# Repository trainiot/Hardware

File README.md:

# Hardware
This git repository contains hardware I am designing to run my small internet connected model train layout.

* [SPI 2 DCC](Spi2Dcc)  
Generates the DCC signal. Controlled through SPI.

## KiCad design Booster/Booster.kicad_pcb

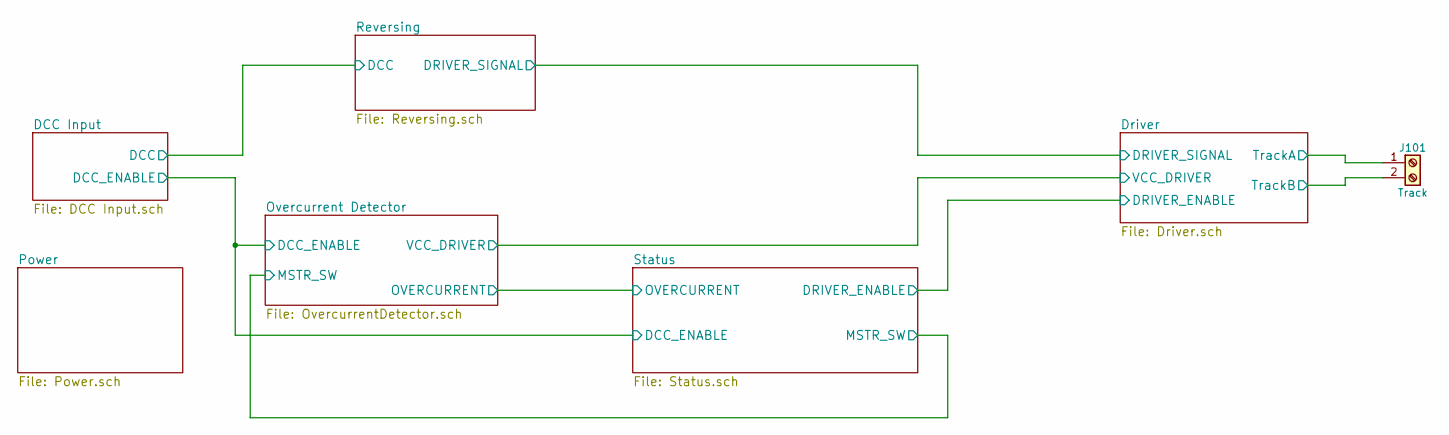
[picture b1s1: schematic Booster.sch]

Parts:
J101: Track; TerminalBlock_bornier-2_P5.08mm

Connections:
/Driver/TrackA: J101.1; also elsewhere on the board
/Driver/TrackB: J101.2; also elsewhere on the board

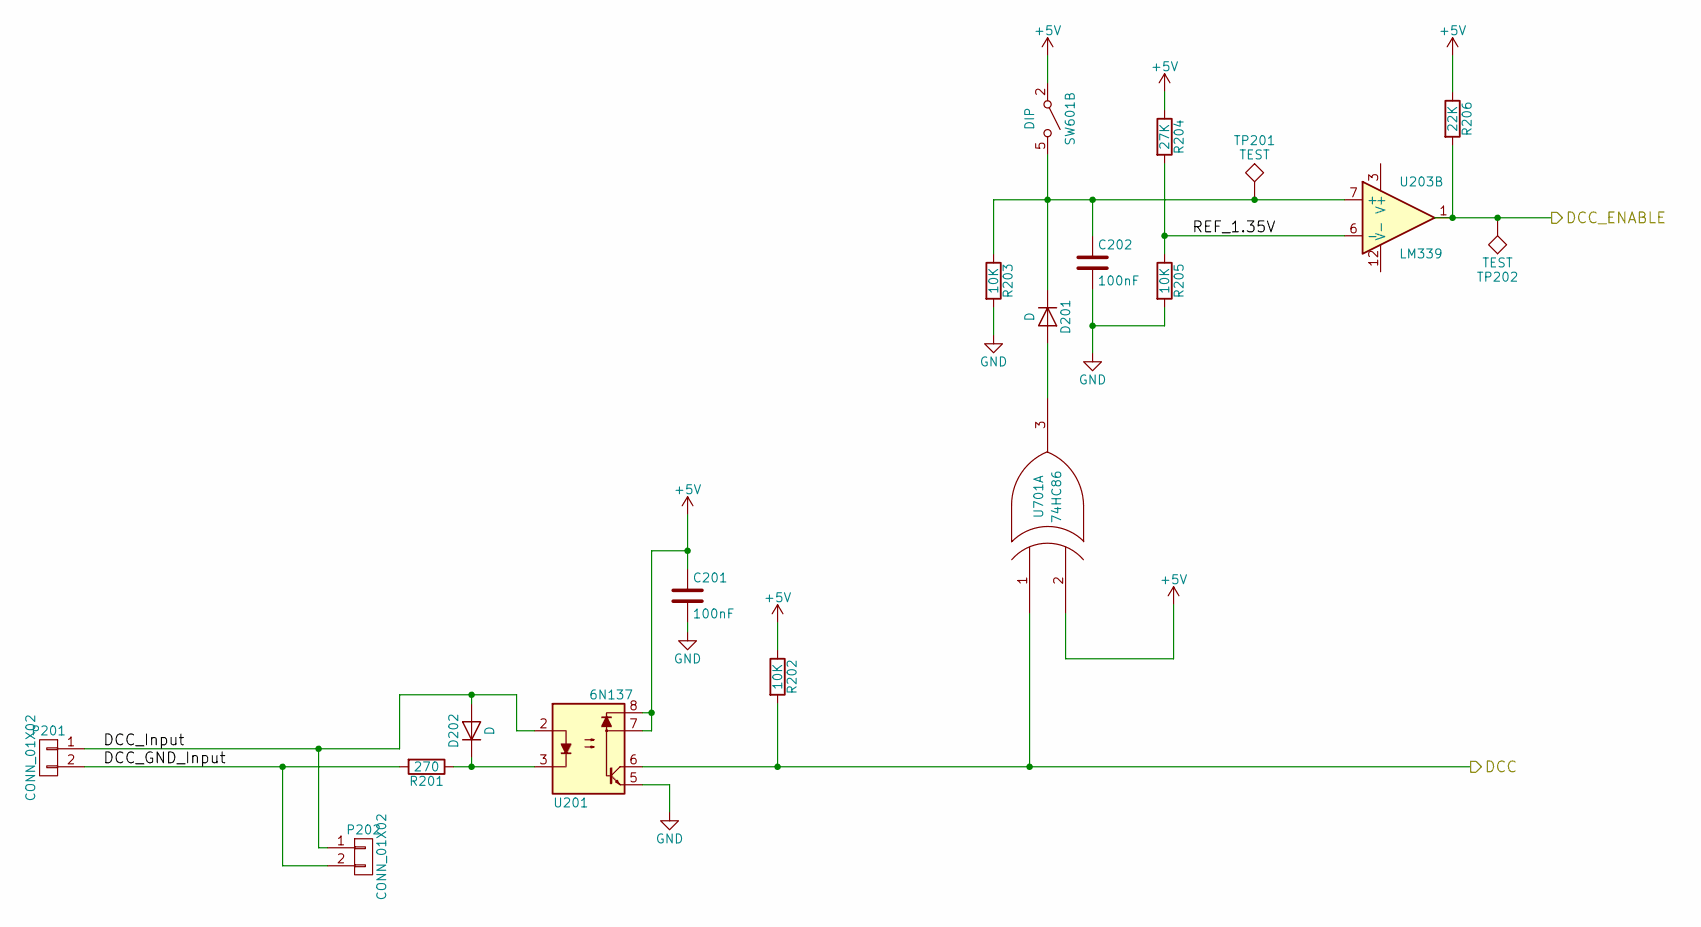
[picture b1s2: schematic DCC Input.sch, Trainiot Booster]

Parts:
C201: 100nF; TO-220-2_Vertical
C202: 100nF; C_0805
D201, D202: D; D_MiniMELF
P201, P202: CONN_01X02; JST_XH_B02B-XH-A_02x2.50mm_Straight
R201: 270; R_0805
R202, R203, R205: 10K; R_0805
R204: 27K; R_0805
R206: 22K; R_0805
SW601: DIP; SW_DIP_x3_W7.62mm_Slide
TP201, TP202: TEST; Measurement_Point_Round-TH_Small
U201: 6N137; SMDIP-8_W9.53mm_Clearance8mm
U203: LM339; SOIC-14_N
U701: 74HC86; SOIC-14_N

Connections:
+5V: C201.1, R202.1, R204.1, R206.1, SW601.2 (A), U201.7, U201.8, U701.2 (IN2), U701.14 (VCC); also elsewhere on the board
+15V: U203.3 (V+); also elsewhere on the board
/DCC Input/DCC: R202.2, U201.6, U701.1 (IN1); also elsewhere on the board
/DCC Input/DCC_ENABLE: R206.2, TP202.1, U203.1; also elsewhere on the board
/DCC Input/DCC_GND_Input: P201.2, P202.2, R201.2
/DCC Input/DCC_Input: D202.2 (A), P201.1, P202.1, U201.2
/DCC Input/REF_1.35V: R204.2, R205.1, U203.6 (-)
GND: C201.2, C202.2, R203.2, R205.2, U201.5, U203.12 (V-), U701.7 (GND); also elsewhere on the board
unnamed: C202.1, D201.1 (K), R203.1, SW601.5 (B), TP201.1, U203.7 (+)
unnamed: D201.2 (A), U701.3 (OUT)
unnamed: D202.1 (K), R201.1, U201.3

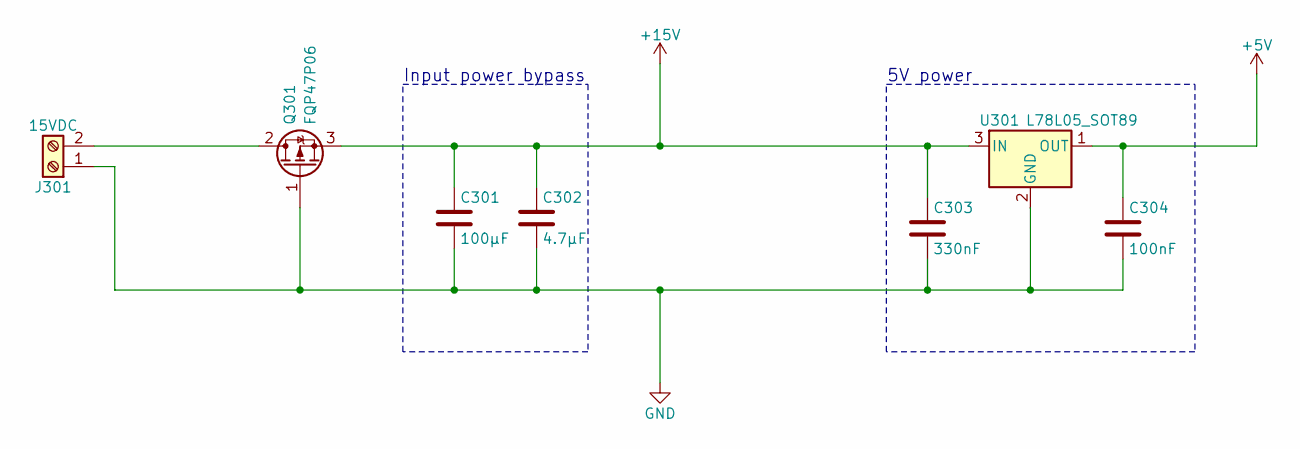
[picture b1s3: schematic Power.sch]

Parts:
C301: 100µF; CP_Radial_D6.3mm_P2.50mm
C302: 4.7µF; CP_Radial_D5.0mm_P2.00mm
C303: 330nF; C_0805
C304: 100nF; C_0805
J301: 15VDC; TerminalBlock_bornier-2_P5.08mm
Q301: FQP47P06; TO-220-3_Vertical
U301: L78L05_SOT89; SOT-89-3

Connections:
+5V: C304.1, U301.1 (OUT); also elsewhere on the board
+15V: C301.1, C302.1, C303.1, Q301.3 (S), U301.3 (IN); also elsewhere on the board
GND: C301.2, C302.2, C303.2, C304.2, J301.1, Q301.1 (G), U301.2 (GND); also elsewhere on the board
unnamed: J301.2, Q301.2 (D)

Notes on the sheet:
Input power bypass
5V power

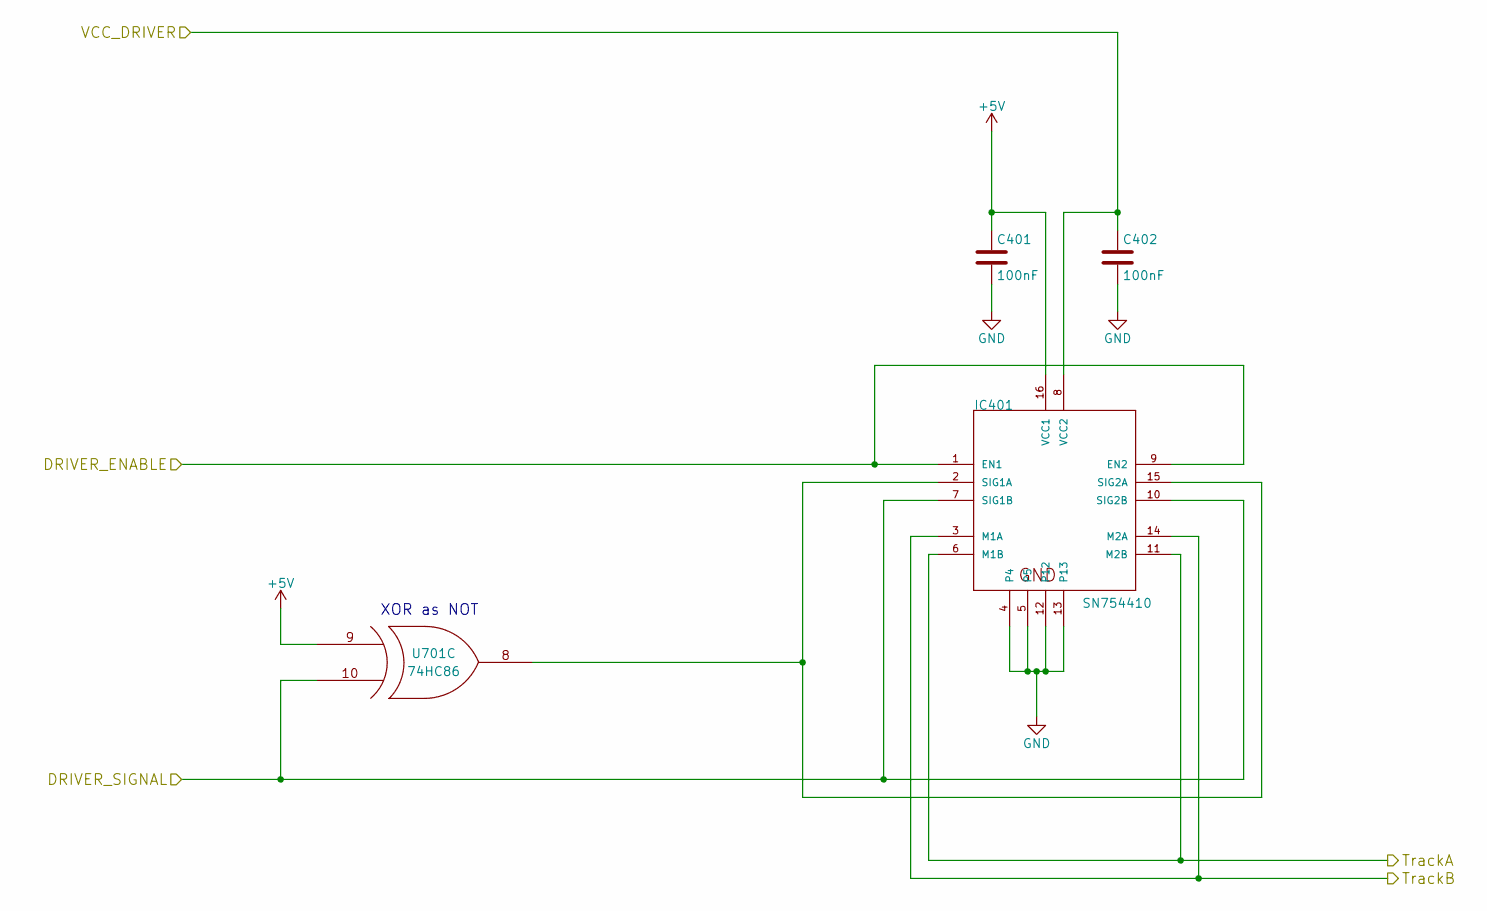
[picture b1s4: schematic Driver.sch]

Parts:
C401, C402: 100nF; C_0805
IC401: SN754410; DIP-16_W7.62mm
U701: 74HC86; SOIC-14_N

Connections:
+5V: C401.1, IC401.16 (VCC1), U701.9 (IN1), U701.14 (VCC); also elsewhere on the board
/Driver/DRIVER_ENABLE: IC401.1 (EN1), IC401.9 (EN2); also elsewhere on the board
/Driver/DRIVER_SIGNAL: IC401.7 (SIG1B), IC401.10 (SIG2B), U701.10 (IN2); also elsewhere on the board
/Driver/TrackA: IC401.6 (M1B), IC401.11 (M2B); also elsewhere on the board
/Driver/TrackB: IC401.3 (M1A), IC401.14 (M2A); also elsewhere on the board
/Driver/VCC_DRIVER: C402.1, IC401.8 (VCC2); also elsewhere on the board
GND: C401.2, C402.2, IC401.4, IC401.5, IC401.12, IC401.13, U701.7 (GND); also elsewhere on the board
unnamed: IC401.2 (SIG1A), IC401.15 (SIG2A), U701.8 (OUT)

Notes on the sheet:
XOR as NOT

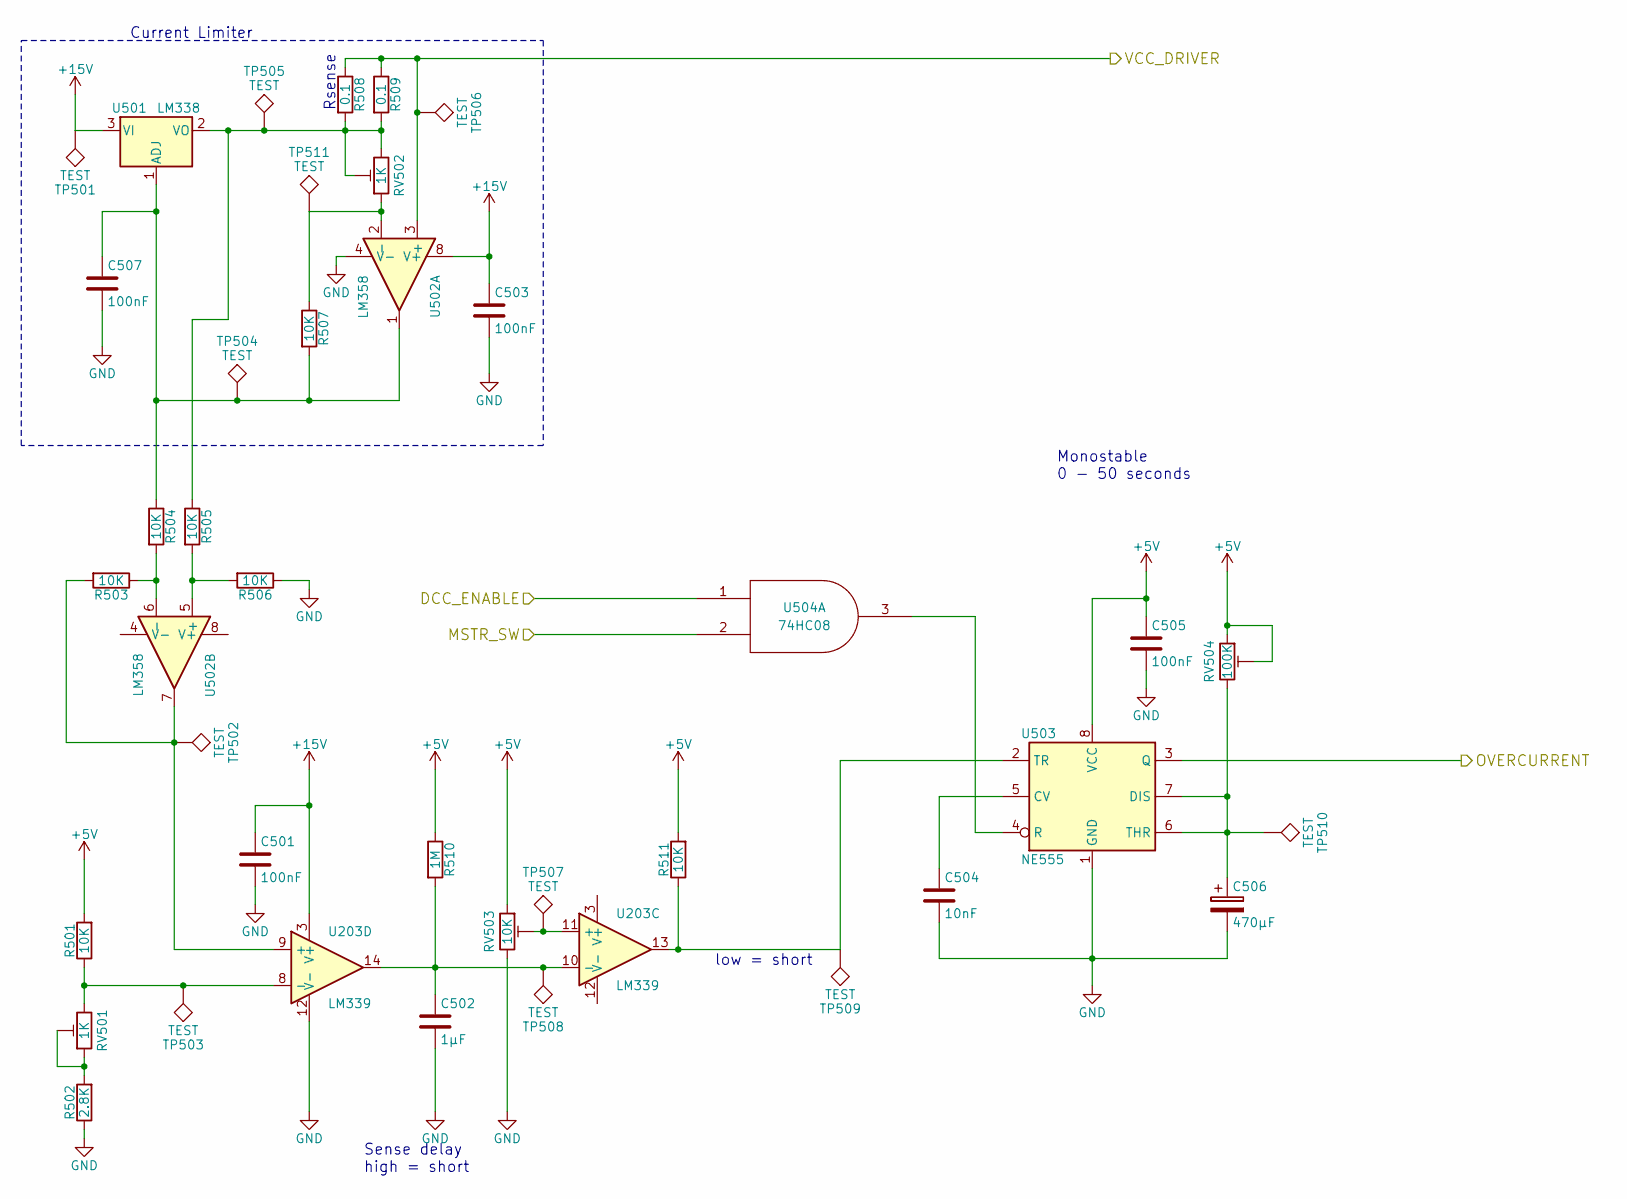
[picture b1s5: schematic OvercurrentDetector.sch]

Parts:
C501, C503, C505, C507: 100nF; C_0805
C502: 1µF; CP_Radial_D5.0mm_P2.50mm
C504: 10nF; C_0805
C506: 470µF; CP_Radial_D10.0mm_P5.00mm
R501, R503, R504, R505, R506, R507, R511: 10K; R_0805
R502: 2.8K; R_0805
R508, R509: 0.1; R_Axial_DIN0207_L6.3mm_D2.5mm_P7.62mm_Horizontal
R510: 1M; R_0805
RV501, RV502: 1K; Potentiometer_Trimmer_Bourns_3296W
RV503: 10K; Potentiometer_Trimmer_Bourns_3296W
RV504: 100K; Potentiometer_Trimmer_Bourns_3296W
TP501, TP502, TP503, TP504, TP505, TP506, TP507, TP508, TP509, TP510, TP511: TEST; Measurement_Point_Round-TH_Small
U203: LM339; SOIC-14_N
U501: LM338; TO-220-3_Vertical_Single_Pin_Heatshield
U502: LM358; SOIC-8-N
U503: NE555; SOIC-8-N
U504: 74HC08; SOIC-14_N

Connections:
+5V: C505.1, R501.2, R510.1, R511.2, RV503.1, RV504.1, RV504.2, U503.8 (VCC), U504.14 (VCC); also elsewhere on the board
+15V: C501.1, C503.1, TP501.1, U203.3 (V+), U501.3 (VI), U502.8 (V+); also elsewhere on the board
/DCC Input/DCC_ENABLE: U504.1; also elsewhere on the board
/Driver/VCC_DRIVER: R508.1, R509.1, TP506.1, U502.3 (+); also elsewhere on the board
/Overcurrent Detector/MSTR_SW: U504.2; also elsewhere on the board
/Overcurrent Detector/OVERCURRENT: U503.3 (Q); also elsewhere on the board
GND: C501.2, C502.2, C503.2, C504.2, C505.2, C506.2, C507.2, R502.1, R506.1, RV503.3, U203.12 (V-), U502.4 (V-), U503.1 (GND), U504.7 (GND); also elsewhere on the board
unnamed: C502.1, R510.2, TP508.1, U203.10 (-), U203.14
unnamed: C504.1, U503.5 (CV)
unnamed: C506.1, RV504.3, TP510.1, U503.6 (THR), U503.7 (DIS)
unnamed: C507.1, R504.1, R507.2, TP504.1, U501.1 (ADJ), U502.1
unnamed: R501.1, RV501.3, TP503.1, U203.8 (-)
unnamed: R502.2, RV501.1, RV501.2
unnamed: R503.1, R504.2, U502.6 (-)
unnamed: R503.2, TP502.1, U203.9 (+), U502.7
unnamed: R505.1, R508.2, R509.2, RV502.2, RV502.3, TP505.1, U501.2 (VO)
unnamed: R505.2, R506.2, U502.5 (+)
unnamed: R507.1, RV502.1, TP511.1, U502.2 (-)
unnamed: R511.1, TP509.1, U203.13, U503.2 (TR)
unnamed: RV503.2, TP507.1, U203.11 (+)
unnamed: U503.4 (R), U504.3

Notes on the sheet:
Current Limiter
Rsense
Sense delay high = short
low = short
Monostable 0 - 50 seconds

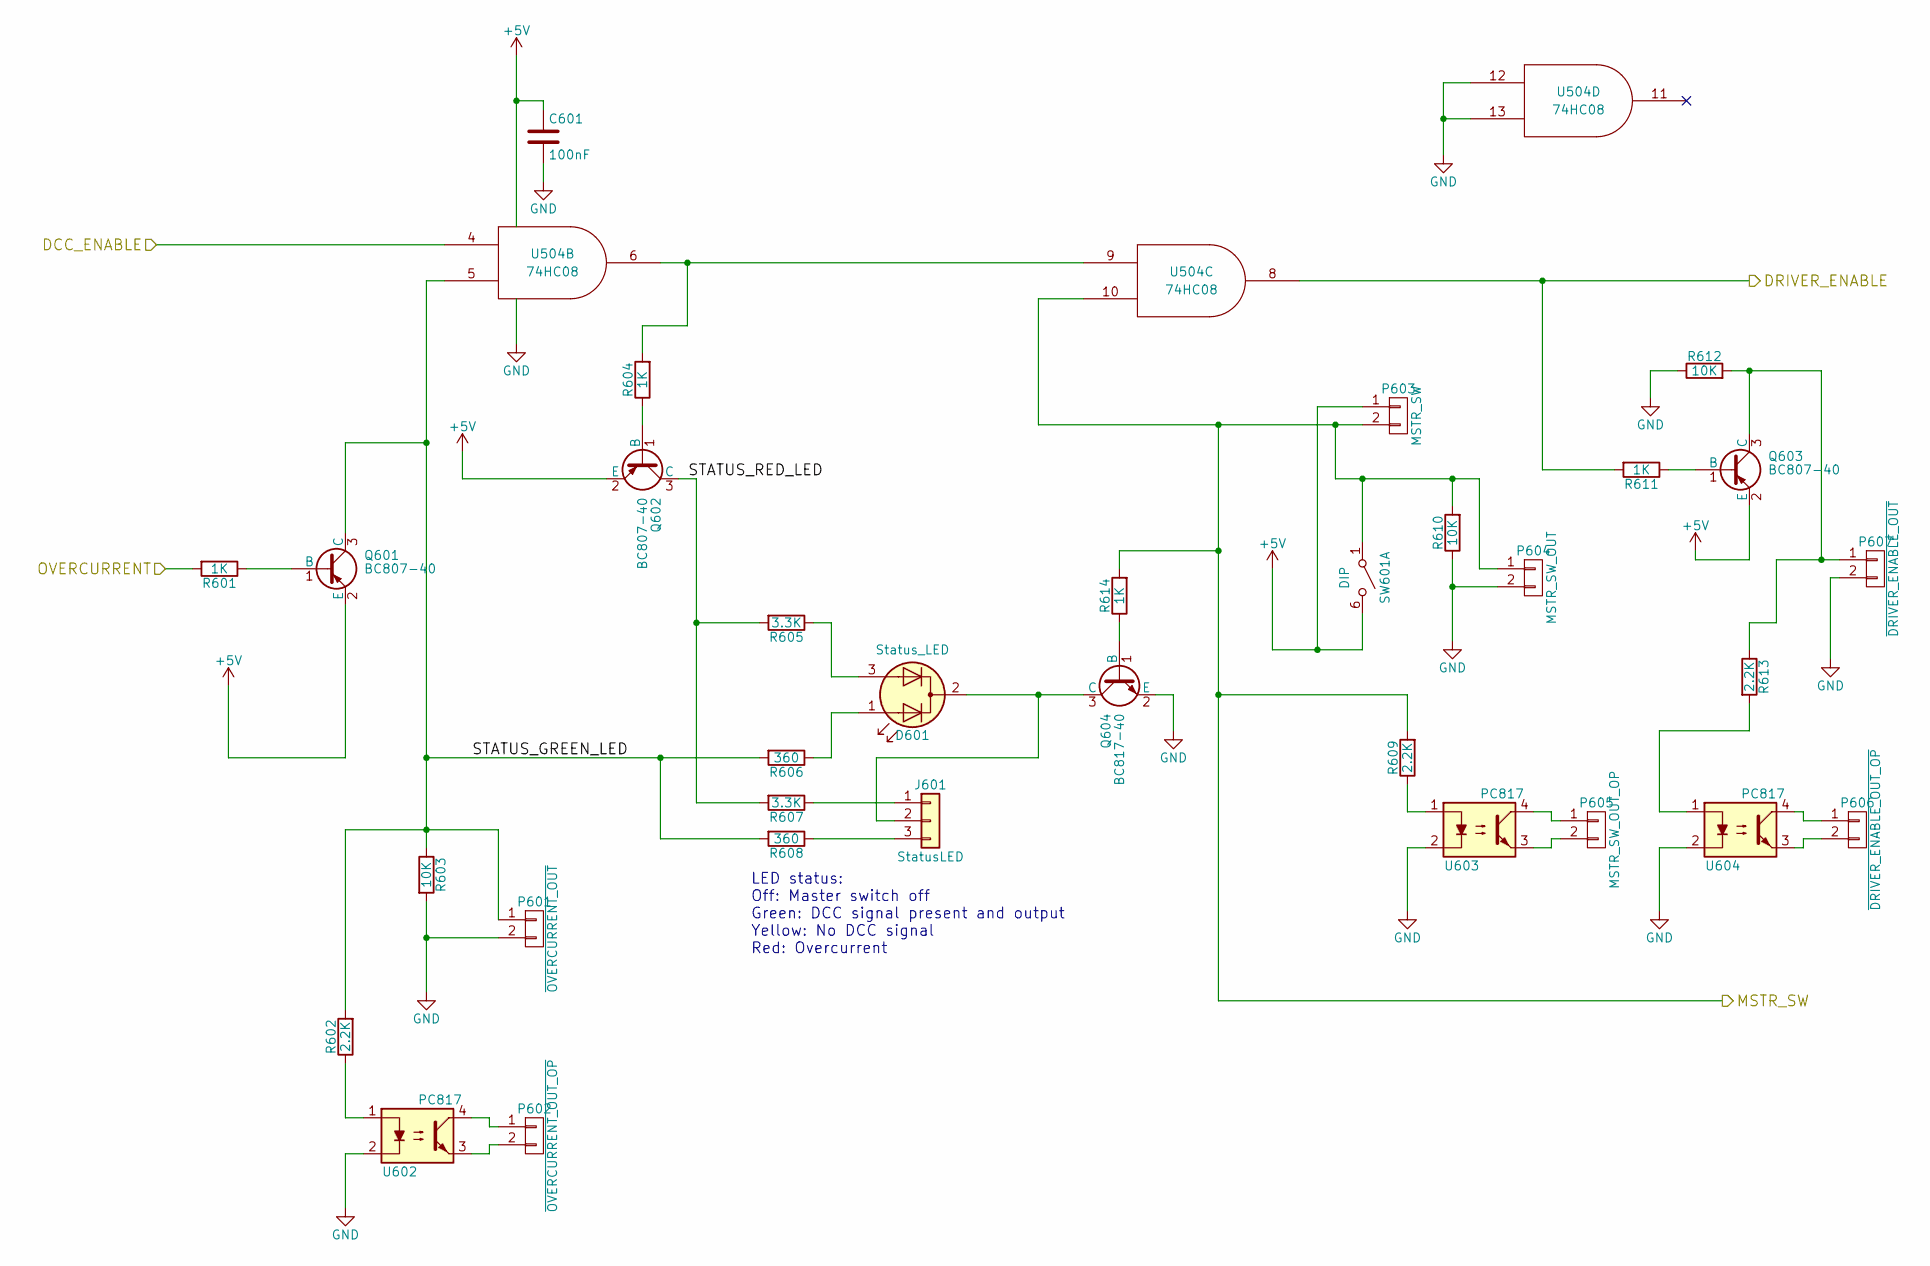
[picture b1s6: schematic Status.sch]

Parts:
C601: 100nF; C_0805
D601: Status_LED; LED_D3.0mm-3
J601: StatusLED; JST_XH_B03B-XH-A_03x2.50mm_Straight
P601: ~OVERCURRENT_OUT; JST_XH_B02B-XH-A_02x2.50mm_Straight
P602: ~OVERCURRENT_OUT_OP; JST_XH_B02B-XH-A_02x2.50mm_Straight
P603: MSTR_SW; JST_XH_B02B-XH-A_02x2.50mm_Straight
P604: MSTR_SW_OUT; JST_XH_B02B-XH-A_02x2.50mm_Straight
P605: MSTR_SW_OUT_OP; JST_XH_B02B-XH-A_02x2.50mm_Straight
P606: ~DRIVER_ENABLE_OUT_OP; JST_XH_B02B-XH-A_02x2.50mm_Straight
P607: ~DRIVER_ENABLE_OUT; JST_XH_B02B-XH-A_02x2.50mm_Straight
Q601, Q602, Q603: BC807-40; SOT-23
Q604: BC817-40; SOT-23
R601, R604, R611, R614: 1K; R_0805
R602, R609, R613: 2.2K; R_0805
R603, R610, R612: 10K; R_0805
R605, R607: 3.3K; R_0805
R606, R608: 360; R_0805
SW601: DIP; SW_DIP_x3_W7.62mm_Slide
U504: 74HC08; SOIC-14_N
U602, U603, U604: PC817; SMDIP-4_W9.53mm_Clearance8mm

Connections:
+5V: C601.1, P603.1, Q601.2 (E), Q602.2 (E), Q603.2 (E), SW601.6 (B), U504.14 (VCC); also elsewhere on the board
/DCC Input/DCC_ENABLE: U504.4; also elsewhere on the board
/Driver/DRIVER_ENABLE: R611.2, U504.8; also elsewhere on the board
/Overcurrent Detector/MSTR_SW: P603.2, P604.1, R609.2, R610.2, R614.2, SW601.1 (A), U504.10; also elsewhere on the board
/Overcurrent Detector/OVERCURRENT: R601.2; also elsewhere on the board
/Status/STATUS_GREEN_LED: P601.1, Q601.3 (C), R602.2, R603.1, R606.2, R608.2, U504.5
/Status/STATUS_RED_LED: Q602.3 (C), R605.2, R607.2
GND: C601.2, P601.2, P604.2, P607.2, Q604.2 (E), R603.2, R610.1, R612.1, U504.7 (GND), U504.12, U504.13, U602.2, U603.2, U604.2; also elsewhere on the board
unnamed: D601.1 (A1), R606.1
unnamed: D601.2 (K), J601.2, Q604.3 (C)
unnamed: D601.3 (A2), R605.1
unnamed: J601.1, R607.1
unnamed: J601.3, R608.1
unnamed: P602.1, U602.4
unnamed: P602.2, U602.3
unnamed: P605.1, U603.4
unnamed: P605.2, U603.3
unnamed: P606.1, U604.4
unnamed: P606.2, U604.3
unnamed: P607.1, Q603.3 (C), R612.2, R613.1
unnamed: Q601.1 (B), R601.1
unnamed: Q602.1 (B), R604.1
unnamed: Q603.1 (B), R611.1
unnamed: Q604.1 (B), R614.1
unnamed: R602.1, U602.1
unnamed: R604.2, U504.6, U504.9
unnamed: R609.1, U603.1
unnamed: R613.2, U604.1

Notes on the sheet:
LED status: Off: Master switch off Green: DCC signal present and output Yellow: No DCC signal Red: Overcurrent

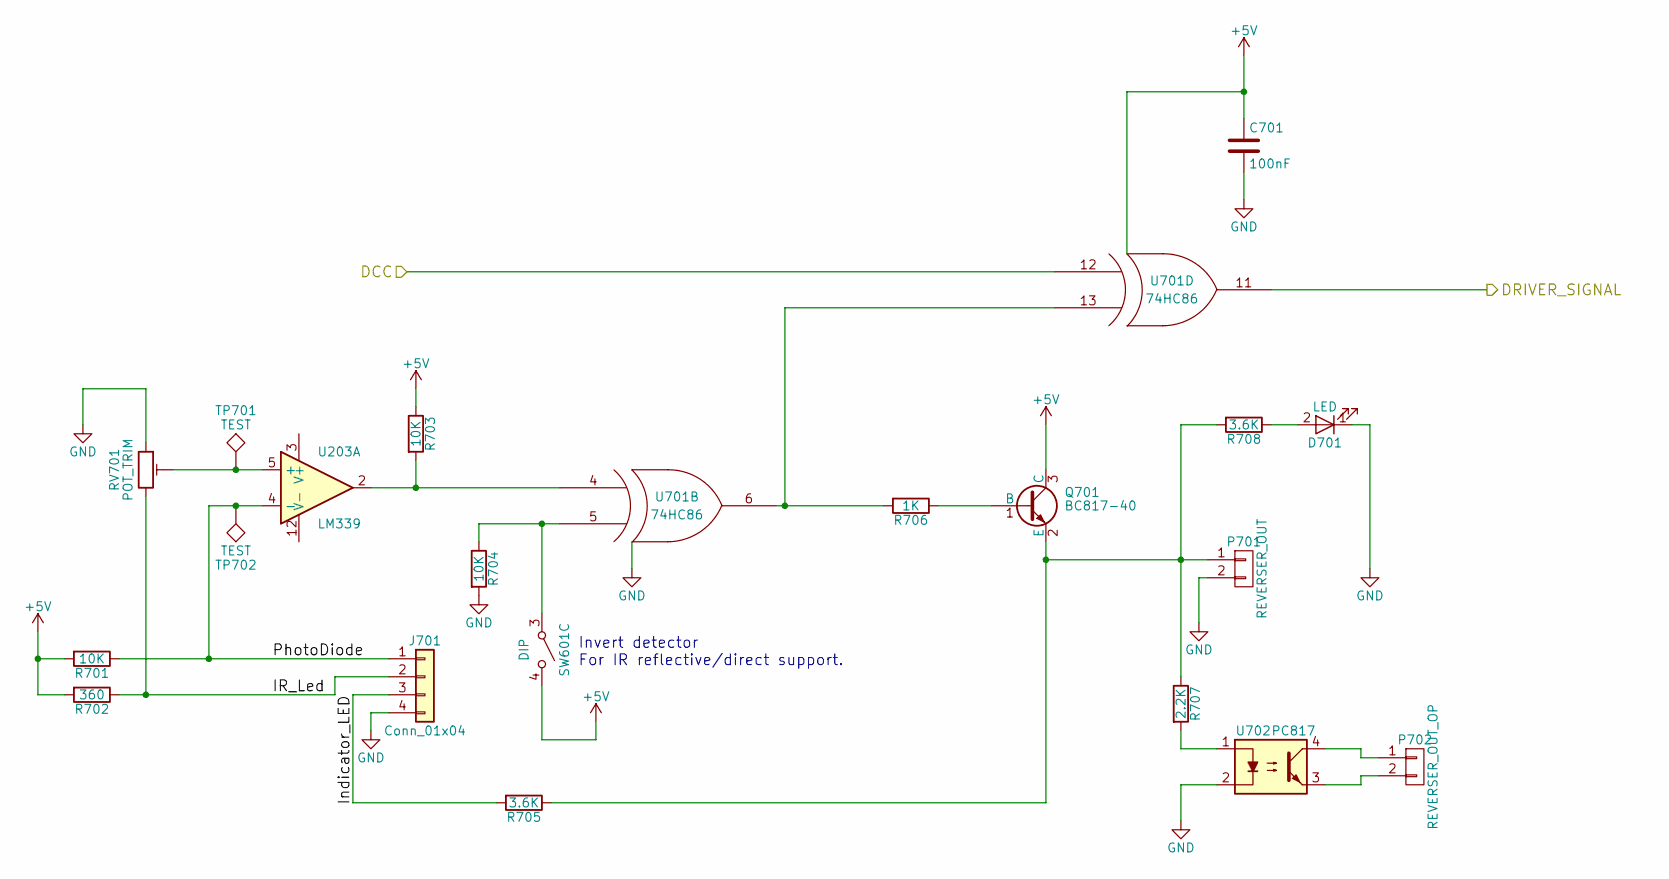
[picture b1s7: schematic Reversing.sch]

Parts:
C701: 100nF; C_0805
D701: LED; LED_D3.0mm
J701: Conn_01x04; JST_XH_B04B-XH-A_04x2.50mm_Straight
P701: REVERSER_OUT; JST_XH_B02B-XH-A_02x2.50mm_Straight
P702: REVERSER_OUT_OP; JST_XH_B02B-XH-A_02x2.50mm_Straight
Q701: BC817-40; SOT-23
R701, R703, R704: 10K; R_0805
R702: 360; R_0805
R705, R708: 3.6K; R_0805
R706: 1K; R_0805
R707: 2.2K; R_0805
RV701: POT_TRIM; Potentiometer_Trimmer_Bourns_3296W
SW601: DIP; SW_DIP_x3_W7.62mm_Slide
TP701, TP702: TEST; Measurement_Point_Round-TH_Small
U203: LM339; SOIC-14_N
U701: 74HC86; SOIC-14_N
U702: PC817; SMDIP-4_W9.53mm_Clearance8mm

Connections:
+5V: C701.1, Q701.3 (C), R701.2, R702.2, R703.1, SW601.4 (B), U701.14 (VCC); also elsewhere on the board
+15V: U203.3 (V+); also elsewhere on the board
/DCC Input/DCC: U701.12 (IN1); also elsewhere on the board
/Driver/DRIVER_SIGNAL: U701.11 (OUT); also elsewhere on the board
/Reversing/IR_Led: J701.2, R702.1, RV701.3
/Reversing/Indicator_LED: J701.3, R705.2
/Reversing/PhotoDiode: J701.1, R701.1, TP702.1, U203.4 (-)
GND: C701.2, D701.1 (K), J701.4, P701.2, R704.2, RV701.1, U203.12 (V-), U701.7 (GND), U702.2; also elsewhere on the board
unnamed: D701.2 (A), R708.1
unnamed: P701.1, Q701.2 (E), R705.1, R707.1, R708.2
unnamed: P702.1, U702.4
unnamed: P702.2, U702.3
unnamed: Q701.1 (B), R706.1
unnamed: R703.2, U203.2, U701.4 (IN1)
unnamed: R704.1, SW601.3 (A), U701.5 (IN2)
unnamed: R706.2, U701.6 (OUT), U701.13 (IN2)
unnamed: R707.2, U702.1
unnamed: RV701.2, TP701.1, U203.5 (+)

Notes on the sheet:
Invert detector For IR reflective/direct support.

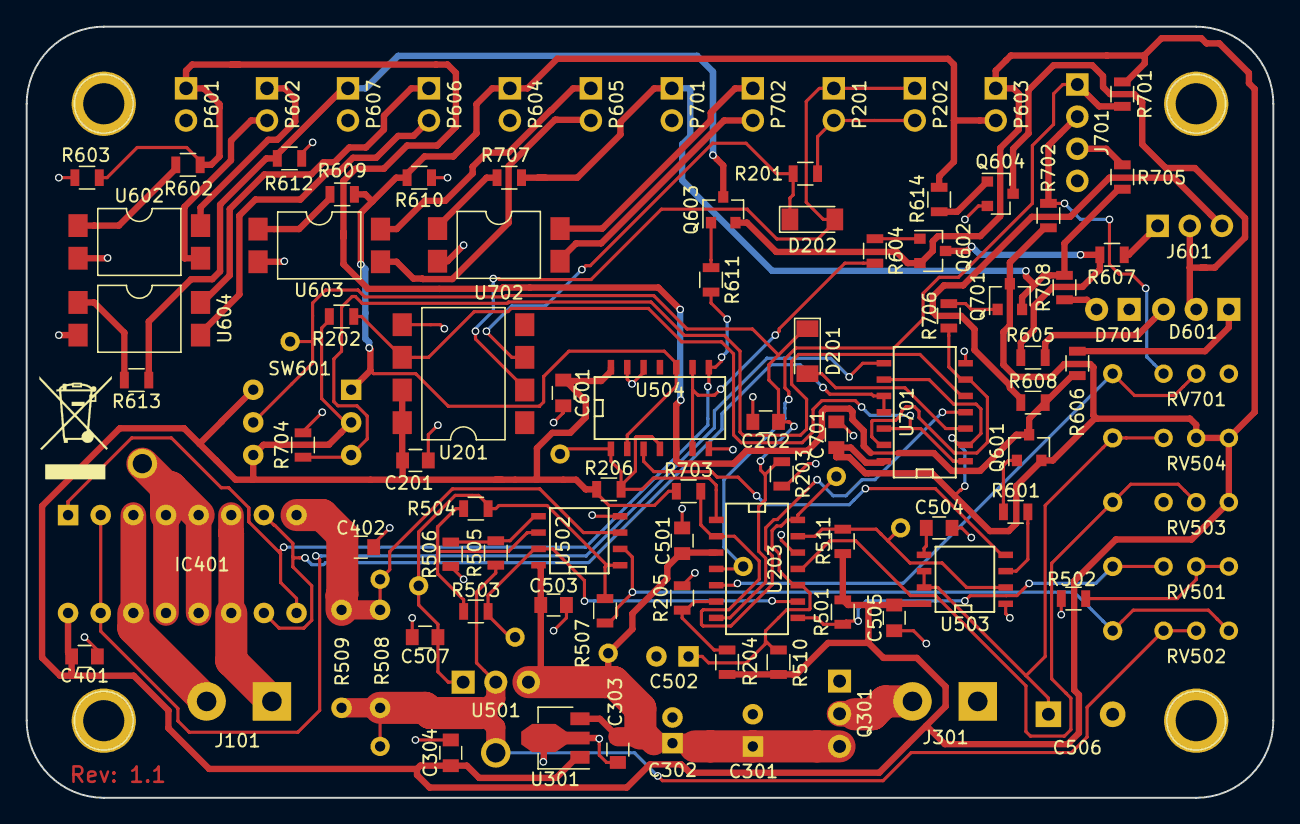
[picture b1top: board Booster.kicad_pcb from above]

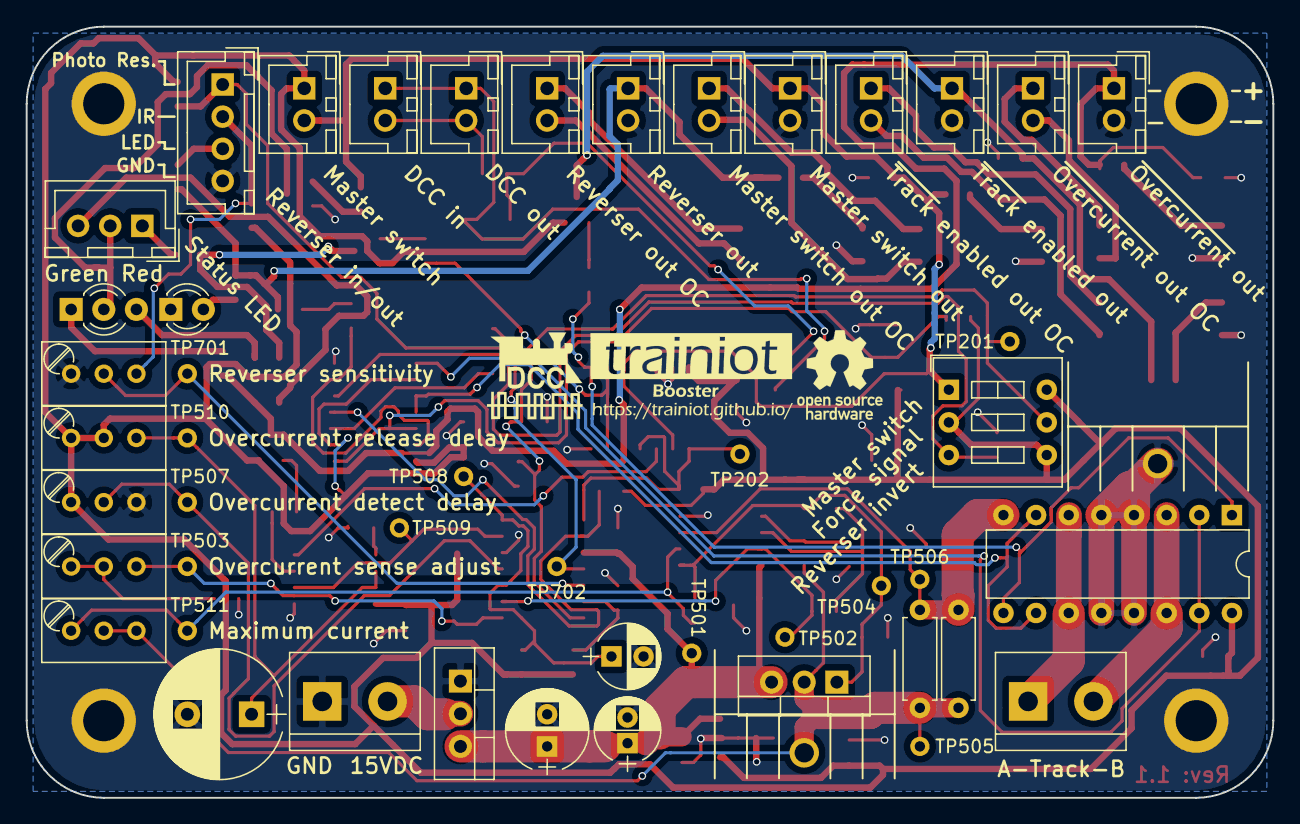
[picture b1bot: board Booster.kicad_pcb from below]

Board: 2 copper layers, 97.0 x 60.0 mm, 115 parts (46 on the bottom side), 69 nets.

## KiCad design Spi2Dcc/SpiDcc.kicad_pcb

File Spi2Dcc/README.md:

# SPI 2 DCC
This hardware module allows generating a DCC signal from any device that can generate an SPI signal. This includes the 
Raspberry PI and most other development boards. Notice this only generates the signal at 3.3V - a booster is required to run the trains at 12V or higher.

**This is neither the cheapest nor the easist way to generate a DCC signal.**  
This was done as a hobby project to see if it is possible to generate the signal using off the shelves logic chips.

If you want something simple and cheap then get a [SPROG](http://www.sprog-dcc.co.uk/about_sprogII.shtml). If you just want it simple,
then get any of the computer enabled DCC command station - for example an [IB-COM](http://www.uhlenbrock.de/de_DE/produkte/digizen/I000C67F-001.htm!ArcEntryInfo=0004.2.I000C67F)
but there are many (mostly newer and better) alternatives.

If you want to play with the electronics and do plan to use a separate booster, try [DCC++](https://github.com/DccPlusPlus/BaseStation) which offers more functionality than this project.

Still crazy enough to hang around here? Read here how the circuit is supposed to work. *Supposed* is an important word here! The hardware has not yet been assembled and no command has been sent to a model train at this moment in time.

## Schematics
### Overview

### Input Connectors
Contains the 6 pin interface to the controlling device and power. It is assumed the 3v3 power soure will originate from the controlling 
device but it is of course possible to use an alternative power source.
Besides the 3v3 and ground connectors you will find the three SPI signals (as the device is write only there is no MISO). The final connection 
"IN_PREAMBLE" can be used to drive an interrupt tracking when the command has been "locked" for transmission and the device is ready to receive
the next DCC command. 

### Command Register

The device holds two DCC commands in shift registers - each command stored in 6 shift registers. 

One set of registers (the input registers) holds the latest command recieved through SPI. When the device starts transmitting
a new command it will copy the command from these registers into the registers used to transmit (the output registers).
If commands are received faster than they can be transmitted they will be lost.

* U501: Counts the number of bits received through the SPI interface. By ignoring the 3 least significent bits this number is effectively devided by 8 providing the number of bytes. It uses SS from the SPI signal to both store the
last command length in the output register and clear the counter so it is ready to count the next command
(using U402E to invert SS as needed by the master counter reset).

* U502 latch: As the device starts transmitting a new DCC command this latch will store the length (in bytes) of the command being transmitted.  
The incoming IN_CMD_END_BIT is used to signal when a new command should be read from the counter and shiftregisters and "locked" in the output registers.

* U402F inverter: If the counter overflows this will disable "Count Enable", ensuring the register stops with a 0 byte command length,
instead of counting up once more potentially reaching a valid command set.

* U302D OR gate: Combines counter bit 6 and 7. If either is set the command is longer than the allowed 6 bytes and the boosters
should be disabled. As there is no need to determine exactly how long the command is - just that it is too long - the two address bits
are not needed on their own.

* U503 Dual 4 to 1 demultiplexer

  * Unit 1: Selects the active output shift register based on the current command length.
A valid command must be 3 to 6 bytes long (both inclusive).  

  * Unit 2: Enable/disable boosters based on the command length. TODO: Copy and improve description of this from the Danish blog

#### Shift Registers
The 12 shift registers used to store the two DCC commands.

* 74HC595 Parallel out registers: The 6 shift registers at the bottom stores the command received through SPI (input registers).
* 74HC164 Parallel in registers: The 6 shift registers at the top holds the command currently being transmitted (output registers).
The incoming IN_CMD_END_BIT signal is used to load the latest command from the input registers when transmitting a new command starts.
If no new command has been received the previous command will be loaded again and retransmitted.

### Clock Generator
A 555 timer circuit used to generate a 58μs clock required by the DCC signal when transmitting 1 bits.

The generated clock has a duty cycle close to 50%. This is not a requirement for the circuit to work - only the timing of the
rising edge is important.

U202A is a flip flop used to derive the 116μs clock required for 0 bits on the DCC protocol.

### State Machine
The state machine is responsible for timing the DCC signal according to the [specifications](http://www.nmra.org/sites/default/files/s-92-2004-07.pdf).

* U401 counter: Specify when the DCC command preamble (15 one bits) should be generated by counting from 0 until 15 where Tc (pin 15) is activated. When this happens the counter is disabled through U402A until the next command starts.
* U402 counter: Specify when the DCC byte preamble (1 zero bit) should be generated. It resets when the preamble is activated. After the preamble it will count from 0-8 repeatedly (so 9 bits in total). U402B is used to reset the counter when it reach 8.
* U302B OR gate: Combines the command and byte preambles generating a signal that indicates where the actual data bits needs to be send. This signal is used to disable the output shift registers when transmitting either preamble.
* U74HC193 counter: Loads the command length as a new command is started, then count down until it reach 0 indicating the command has completed and the command end bit (a single one bit) should be generated and the next command loaded.

### DCC Generator
Generates 0 or 1 DCC bits based on the output from the DCC State Machine and the current output command from the Command Register.

* U301A two to one demultiplexer: Selects the data from the output command shift register if the current state specifies a command byte is being transmitted. If a command byte is currently not transmitted it will select IN_CMD_END_BIT which will be 0 (the expected value for a data byte preamble but not for a command preamble) unless the last byte has been send (where it will be 1 as expected for a DCC command end bit). 

* U302A OR Gate: As the output from U301A is 0 in the command preamble this OR gate is required to generate the preamble.

* U301B two to one demultiplexer: Selectes the 58μs clock if the assembled DCC command bit is 1. If it is 0 the 116μs clock is selected.

* U202B flip flop: Inverts the generated DCC signal based on the selected clock. This generates the final DCC signal which is also used as a clock driving the entire circuit as the DCC signal raising edge occurs when a bit has been transmitted.

### Panel and Sensors
Provides connectors for a front panel as well as sensor output that can be used for further automation.

* Q701 Drives the red color in two bi color LEDs (one on the board, one in the front panel). The red is turned off when a valid signal (command length of 3-6 bytes) is being generated. This results in green LEDs. It also drives the sensor output P702. If no valid sensor signal is generated both red and green LED colors will be lit resulting in a yellow light.

* When the Master Switch (P703 front panel installation or P704 bypass jumper) are both open the LEDs will turn off as the cathodes of the LEDs will be driven high. The sensor output P706 will indicate if the switch (or bypass) is open or closed.

* U302C OR gate: Activates boosters through Q703 (with sensor output P705) when there is **both** a valid command **and** the master switch (or bypass) is closed.

### Booster Connectors
Provides connectors for one or more DCC boosters.

* U301C two to one demultiplexer: Always select high if BOOSTER_ENABLE is high - if not it selects the DCC signal. As the output is inverted by Q901 this results in the DCC output always being low (0) if BOOSTER_ENABLE is low. This would allow using boosters that enable/disable based on an active DCC signal instead of relying on the BOOSTER_ENABLE pin.

* Q901: Enables relative high current boosters - specifically to support multiple boosters using optocouplers.

The current schematic has 4 booster connectors - P901, P902, P904, and P905. This number is based on the space available on the PCB after layout. If needed Q901 should be able to drive significantly more boosters.

There is no transistor driving BOOSTER_ENABLE on this schematics as it is already driven by Q703 on the "Panel and Sensors" schematic.

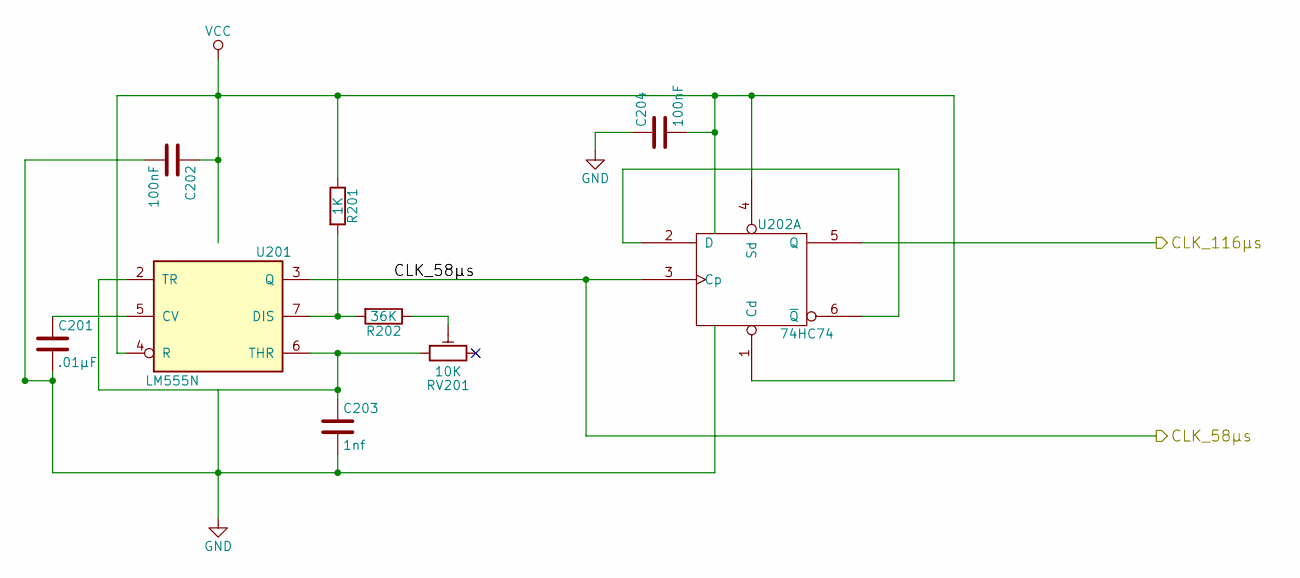
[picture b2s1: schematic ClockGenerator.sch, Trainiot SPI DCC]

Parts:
C201: .01μF; C_0603
C202, C204: 100nF; C_0603
C203: 1nf; C_0603
R201: 1K; R_0603
R202: 36K; R_0603
RV201: 10K; Potentiometer_Trimmer_Bourns_3296W
U201: LM555N; SOIC-8-N
U202: 74HC74; SOIC-14_N

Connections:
/ClockGenerator/CLK_58μs: U201.3 (Q), U202.3 (Cp); also elsewhere on the board
/ClockGenerator/CLK_116μs: U202.5 (Q); also elsewhere on the board
GND: C201.2, C202.2, C203.2, C204.1, U201.1 (GND), U202.7 (GND); also elsewhere on the board
unnamed: C201.1, U201.5 (CV)
unnamed: C203.1, RV201.1, U201.2 (TR), U201.6 (THR)
unnamed: R201.2, R202.2, U201.7 (DIS)
unnamed: R202.1, RV201.2
unnamed: U202.2 (D), U202.6 (~Q)
VCC: C202.1, C204.2, R201.1, U201.4 (R), U201.8 (VCC), U202.1 (Cd), U202.4 (Sd), U202.14 (VCC); also elsewhere on the board

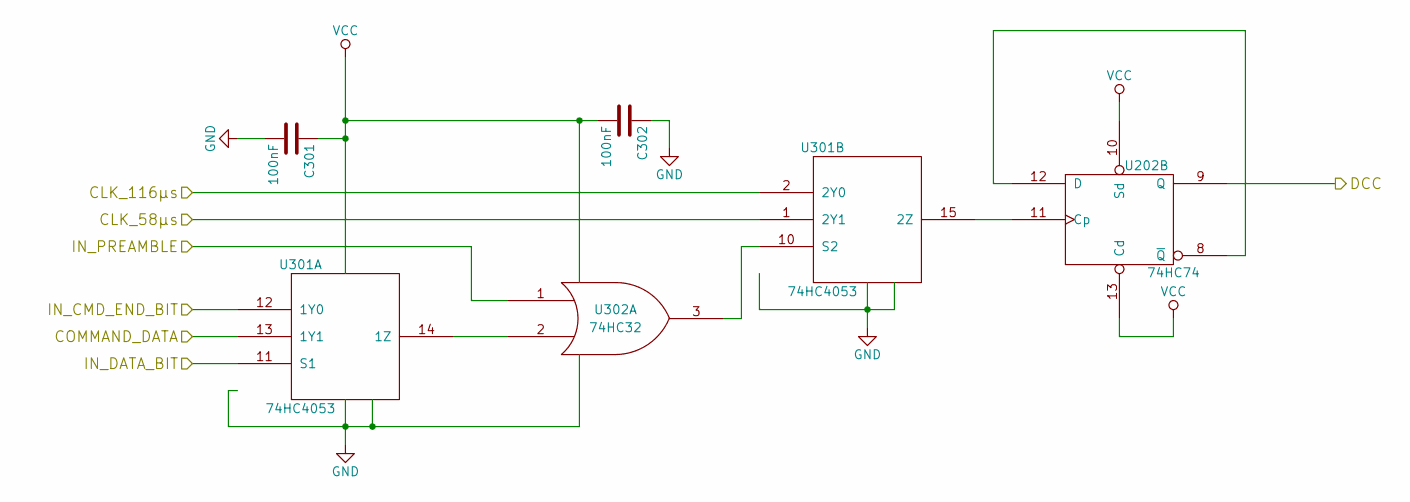
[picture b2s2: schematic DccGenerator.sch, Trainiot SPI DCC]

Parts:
C301, C302: 100nF; C_0603
U202: 74HC74; SOIC-14_N
U301: 74HC4053; SO-16-N
U302: 74HC32; SOIC-14_N

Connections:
/Booster Connectors/DCC: U202.9 (Q); also elsewhere on the board
/ClockGenerator/CLK_58μs: U301.1 (2Y1); also elsewhere on the board
/ClockGenerator/CLK_116μs: U301.2 (2Y0); also elsewhere on the board
/Command Register/COMMAND_DATA: U301.13 (1Y1); also elsewhere on the board
/Command Register/IN_CMD_END_BIT: U301.12 (1Y0); also elsewhere on the board
/DCC Generator/IN_DATA_BIT: U301.11 (S1); also elsewhere on the board
/DCC Generator/IN_PREAMBLE: U302.1; also elsewhere on the board
GND: C301.2, C302.1, U202.7 (GND), U301.6 (E), U301.7 (VEE), U301.8 (GND), U302.7 (GND); also elsewhere on the board
unnamed: U202.11 (Cp), U301.15 (2Z)
unnamed: U202.8 (~Q), U202.12 (D)
unnamed: U301.10 (S2), U302.3
unnamed: U301.14 (1Z), U302.2
VCC: C301.1, C302.2, U202.10 (Sd), U202.13 (Cd), U202.14 (VCC), U301.16 (VDD), U302.14 (VCC); also elsewhere on the board
